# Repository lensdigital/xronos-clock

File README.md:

Xronos (from greek Χρόνος [kronos] which means Time) Clock is not your average Alarm clock.  
It’s open source, hackable and customizable device.  
It has a stylish look, hand made, and it Talks! 
Heck it will even tell you temperature inside your room or from a remote sensor!
Xronos has internal backup battery that will allow it to keep time if you forgot to plug in … if it’s just for an hour or … for a year or two!  
All settings are saved to flash memory (EEPROM), so you don’t have to worry about power loss. All your alarm settings and preference will be there when power comes back on!
Since all audio files are kept on SD card inside, you can even change alarm tones, or replace voice prompts with your own
Xronos has 3 cool looking durable arcade buttons that give you simple access to all of it’s features.

Note: Please do not use V2 for Xronos 2 Clock anymore. V2 Firmware is no longer maintained, but V3 will work with Xronos 2 Clock as well as with upcoming Xronos 3 clocks.

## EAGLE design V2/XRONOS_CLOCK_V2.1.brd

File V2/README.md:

V2 is No longer supported or updated.  Please use V3 firmware as it has backwards compability to Xronos 2 clocks.

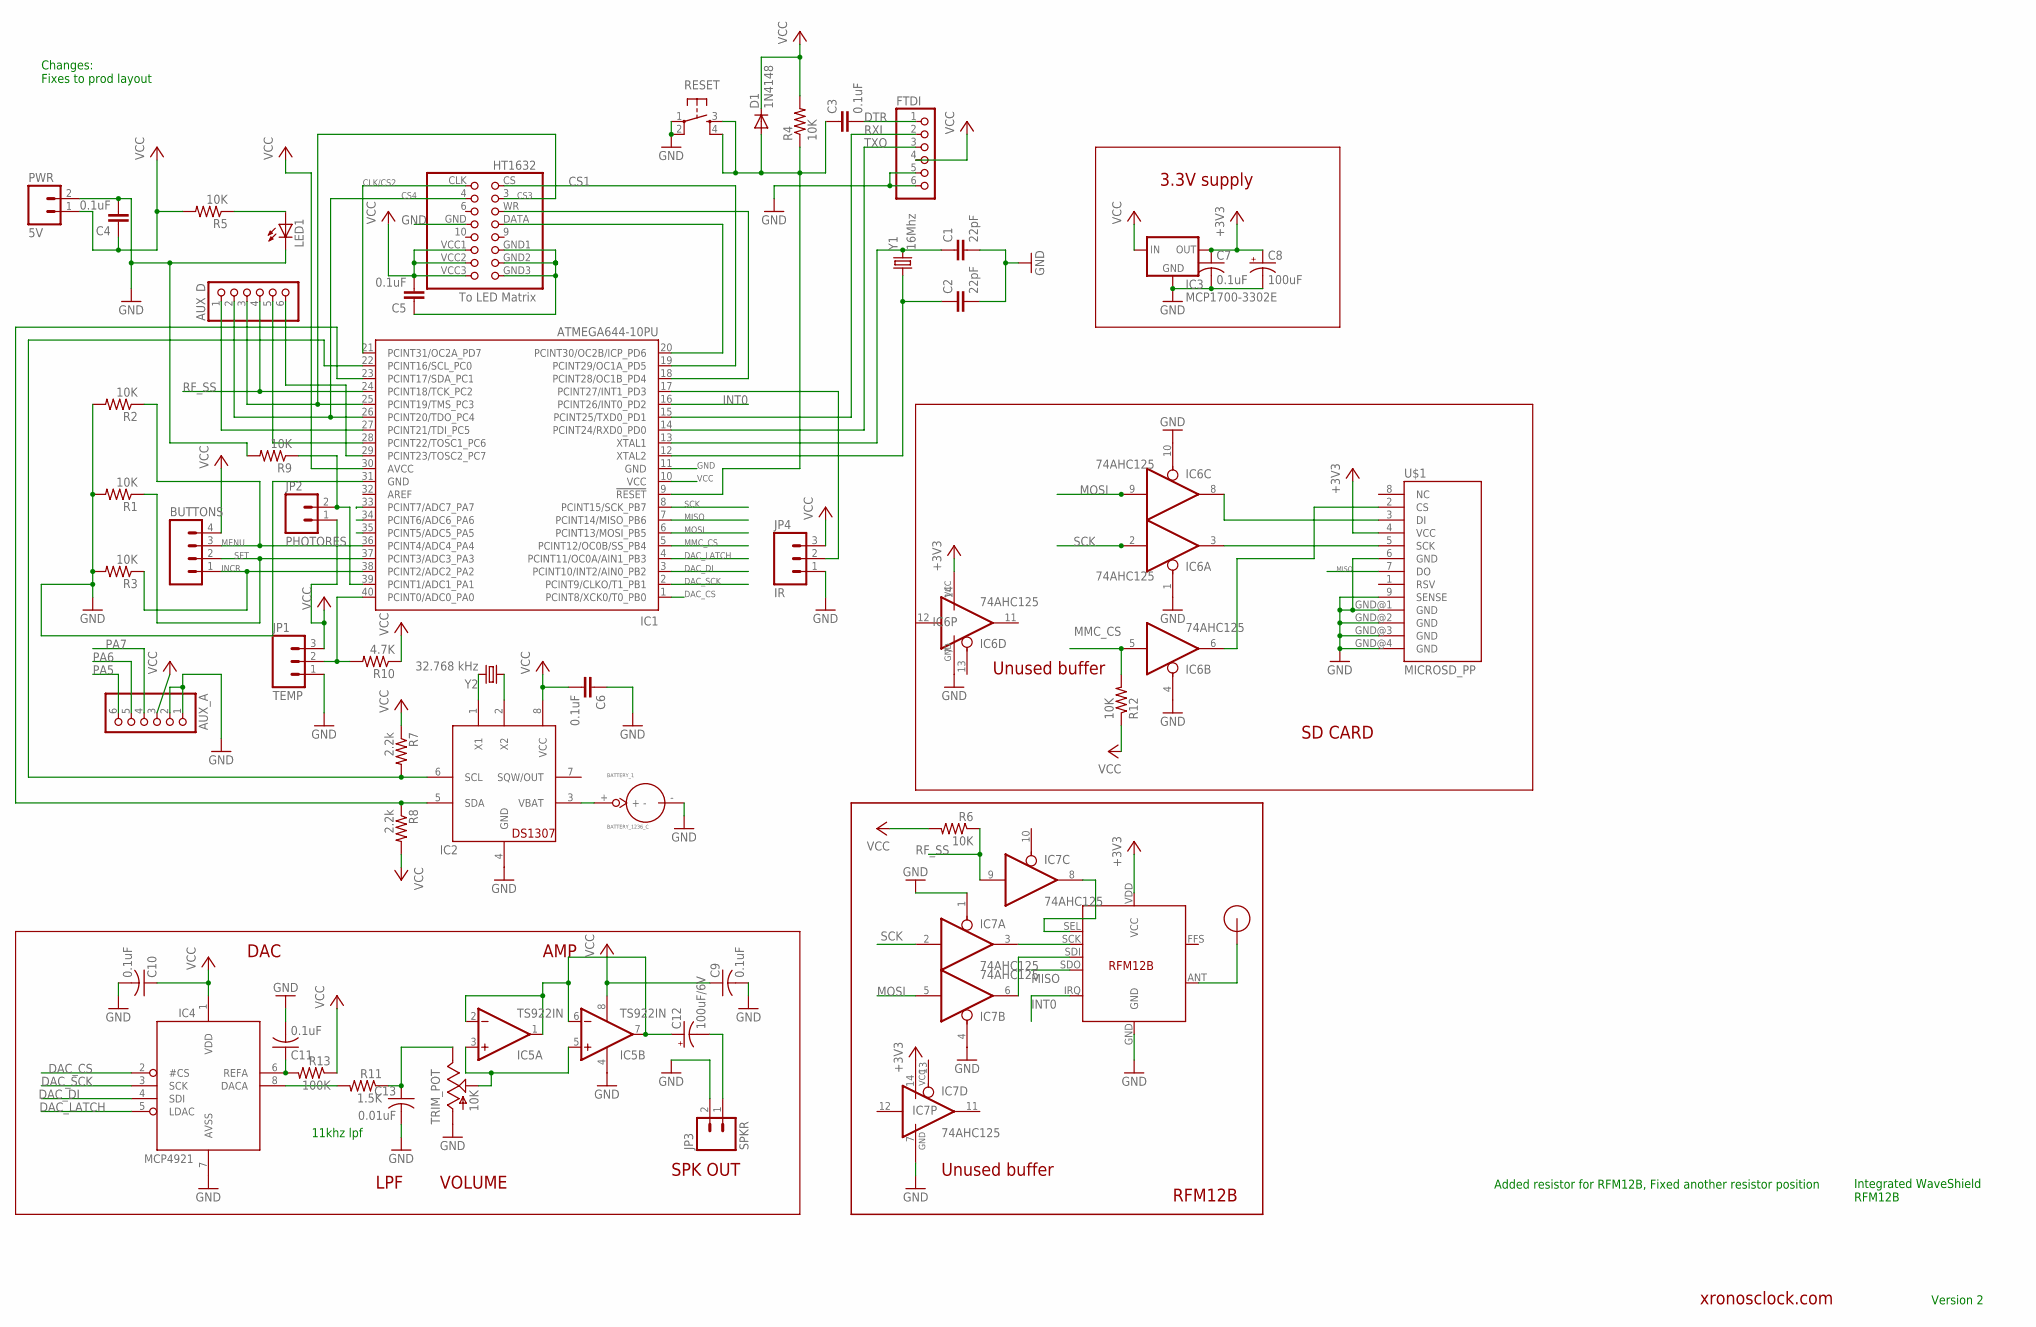
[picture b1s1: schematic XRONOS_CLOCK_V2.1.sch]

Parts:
AUX_A: PINHD-1X6; 1X06
AUX_D: PINHD-1X6; 1X06
BATTERY_1: BATTERY_1236_C
BUTTONS: M04POLAR; MOLEX-1X4
C1, C2: 22pF; C025-024X044
C3, C4, C5, C6: 0.1uF; C025-024X044
C7, C9, C10, C11: 0.1uF; C025-025X050
C8: 100uF; E2,5-5
C12: 100uF/6V; E2,5-5
C13: 0.01uF; C025-025X050
D1: 1N4148; DO35-7
FTDI: PINHD-1X6; 1X06
HT1632: To LED Matrix; IDC2X08
IC1: ATMEGA644-10PU; DIL40
IC2: DS1307; DIL08
IC3: MCP1700-3302E; TO92
IC4: MCP4921; DIL08
IC5: TS922IN; DIL08
IC6: 74AHC125; DIL14-LARDO
IC7: 74AHC125; DIL14
JP1: TEMP; MOLEX-1X3
JP2: PHOTORES; MOLEX-1X2
JP3: SPKR; MOLEX-1X2
JP4: IR; MOLEX-1X3_LOCK
LED1: LED-3MM-NO_SILK; LED3MM-NS
PWR: 5V; MOLEX-1X2
R1, R2, R3, R4, R5, R9: 10K; AXIAL-0.3EZ
R6, R12: 10K; AXIAL-0.3
R7, R8: 2.2k; AXIAL-0.3EZ
R10: 4.7K; AXIAL-0.3EZ
R11: 1.5K; AXIAL-0.3
R13: 100K; AXIAL-0.3
RESET: TAC_SWITCHPTH; TACTILE-PTH
TRIM_POT: 10K; B25P
U$1: MICROSD_PP
U$2: RFM12B
U$3: RFM12B_ANTENNA; RFM12B-ANTENNA
Y1: 16Mhz; HC49US
Y2: 32.768 kHz; TC26HEZ

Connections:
+3V3: C7.1, C8.+, IC3.3 (OUT), IC6.14 (VCC), IC7.14 (VCC), U$1.4 (VCC), U$2.VDD (VCC)
ADJ: IC1.40 (PCINT0/ADC0_PA0), JP1.2, R10.P$2 (2)
CLK/CS2: HT1632.CLK (2), IC1.21 (PCINT31/OC2A_PD7)
CS1: HT1632.CS (1), IC1.19 (PCINT29/OC1A_PD5)
CS3: AUX_D.3, HT1632.3, IC1.25 (PCINT19/TMS_PC3)
CS4: AUX_D.2, HT1632.4, IC1.26 (PCINT20/TDO_PC4)
DAC_CS: IC1.1 (PCINT8/XCK0/T0_PB0), IC4.2 (#CS)
DAC_DI: IC1.3 (PCINT10/INT2/AIN0_PB2), IC4.4 (SDI)
DAC_LATCH: IC1.4 (PCINT11/OC0A/AIN1_PB3), IC4.5 (LDAC)
DAC_SCK: IC1.2 (PCINT9/CLKO/T1_PB1), IC4.3 (SCK)
DATA: HT1632.DATA (7), IC1.20 (PCINT30/OC2B/ICP_PD6)
DTR: C3.2, FTDI.1
GND: AUX_A.1, AUX_A.2, BATTERY_1.-, C1.2, C2.2, C4.2, C6.1, C7.2, C8.-, C9.2, C10.2, C11.2, C13.2, FTDI.5, FTDI.6, HT1632.GND (8), IC1.11 (GND), IC1.31 (GND), IC2.4 (GND), IC3.1 (GND), IC4.7 (AVSS), IC5.4 (V-), IC6.1 (OE), IC6.4 (OE), IC6.7 (GND), IC6.10 (OE), IC7.1 (OE), IC7.4 (OE), IC7.7 (GND), JP1.1, JP3.2, JP4.1, LED1.K (C), PWR.2, R1.P$2 (2), R2.P$2 (2), R3.P$2 (2), R9.P$2 (2), RESET.1, RESET.2, TRIM_POT.A, U$1.6 (GND), U$1.9 (SENSE), U$1.GND@1 (GND), U$1.GND@2 (GND), U$1.GND@3 (GND), U$1.GND@4 (GND), U$2.GND
INCR: BUTTONS.1, IC1.38 (PCINT2/ADC2_PA2), R3.P$1 (1)
INT0: IC1.16 (PCINT26/INT0_PD2), U$2.IRQ
MENU: BUTTONS.3, IC1.36 (PCINT4/ADC4_PA4), R2.P$1 (1)
MISO: IC1.7 (PCINT14/MISO_PB6), U$1.7 (DO), U$2.SDO
MMC_CS: IC1.5 (PCINT12/OC0B/SS_PB4), IC6.5 (I), R12.P$2 (2)
MOSI: IC1.6 (PCINT13/MOSI_PB5), IC6.9 (I), IC7.5 (I)
unnamed: U$2.ANT, U$3.P$1
unnamed: C5.1, HT1632.GND1 (11), HT1632.GND2 (13), HT1632.GND3 (15)
unnamed: IC2.2 (X2), Y2.1
unnamed: IC2.1 (X1), Y2.2
unnamed: C1.1, IC1.13 (XTAL1), Y1.2
unnamed: BATTERY_1.+, IC2.3 (VBAT)
unnamed: IC7.8 (O), U$2.SEL
unnamed: IC1.17 (PCINT27/INT1_PD3), JP4.2
unnamed: C2.1, IC1.12 (XTAL2), Y1.1
unnamed: AUX_D.1, IC1.27 (PCINT21/TDI_PC5)
unnamed: IC1.39 (PCINT1/ADC1_PA1), JP2.2, R9.P$1 (1)
unnamed: AUX_D.5, IC1.28 (PCINT22/TOSC1_PC6)
unnamed: AUX_D.6, IC1.29 (PCINT23/TOSC2_PC7)
unnamed: IC6.8 (O), U$1.3 (DI)
unnamed: LED1.A, R5.P$1 (1)
unnamed: IC6.3 (O), U$1.5 (SCK)
unnamed: IC6.6 (O), U$1.2 (CS)
unnamed: IC4.8 (DACA), R11.P$2 (2)
unnamed: C12.-, JP3.1
unnamed: C12.+, IC5.1 (OUT), IC5.2 (-IN), IC5.6 (-IN), IC5.7 (OUT)
unnamed: C11.1, IC4.6 (REFA), R13.P$2 (2)
unnamed: IC5.3 (+IN), IC5.5 (+IN), TRIM_POT.S
unnamed: C13.1, R11.P$1 (1), TRIM_POT.E
unnamed: IC7.6 (O), U$2.SDI
unnamed: IC7.3 (O), U$2.SCK
PA5: AUX_A.6, IC1.35 (PCINT5/ADC5_PA5)
PA6: AUX_A.5, IC1.34 (PCINT6/ADC6_PA6)
PA7: AUX_A.4, IC1.33 (PCINT7/ADC7_PA7)
RESET: C3.1, D1.A, IC1.9 (!RESET), R4.P$1 (1), RESET.3, RESET.4
RF_SS: AUX_D.4, IC1.24 (PCINT18/TCK_PC2), IC7.9 (I), R6.P$1 (1)
RXI: FTDI.2, IC1.15 (PCINT25/TXD0_PD1)
SCK: IC1.8 (PCINT15/SCK_PB7), IC6.2 (I), IC7.2 (I)
SCL: IC1.23 (PCINT17/SDA_PC1), IC2.5 (SDA), R8.P$1 (1)
SDA: IC1.22 (PCINT16/SCL_PC0), IC2.6 (SCL), R7.P$2 (2)
SET: BUTTONS.2, IC1.37 (PCINT3/ADC3_PA3), R1.P$1 (1)
TXO: FTDI.3, IC1.14 (PCINT24/RXD0_PD0)
VCC: AUX_A.3, BUTTONS.4, C4.1, C5.2, C6.2, C9.1, C10.1, D1.C, FTDI.4, HT1632.VCC1 (12), HT1632.VCC2 (14), HT1632.VCC3 (16), IC1.10 (VCC), IC1.30 (AVCC), IC2.8 (VCC), IC3.2 (IN), IC4.1 (VDD), IC5.8 (V+), JP1.3, JP2.1, JP4.3, PWR.1, R4.P$2 (2), R5.P$2 (2), R6.P$2 (2), R7.P$1 (1), R8.P$2 (2), R10.P$1 (1), R12.P$1 (1), R13.P$1 (1)
WR: HT1632.WR (5), IC1.18 (PCINT28/OC1B_PD4)

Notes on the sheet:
Version 2
Changes: Fixes to prod layout
Integrated WaveShield RFM12B
11khz lpf
DAC
VOLUME
LPF
AMP
SPK OUT
SD CARD
3.3V supply
Unused buffer
RFM12B
xronosclock.com
Added resistor for RFM12B, Fixed another resistor position

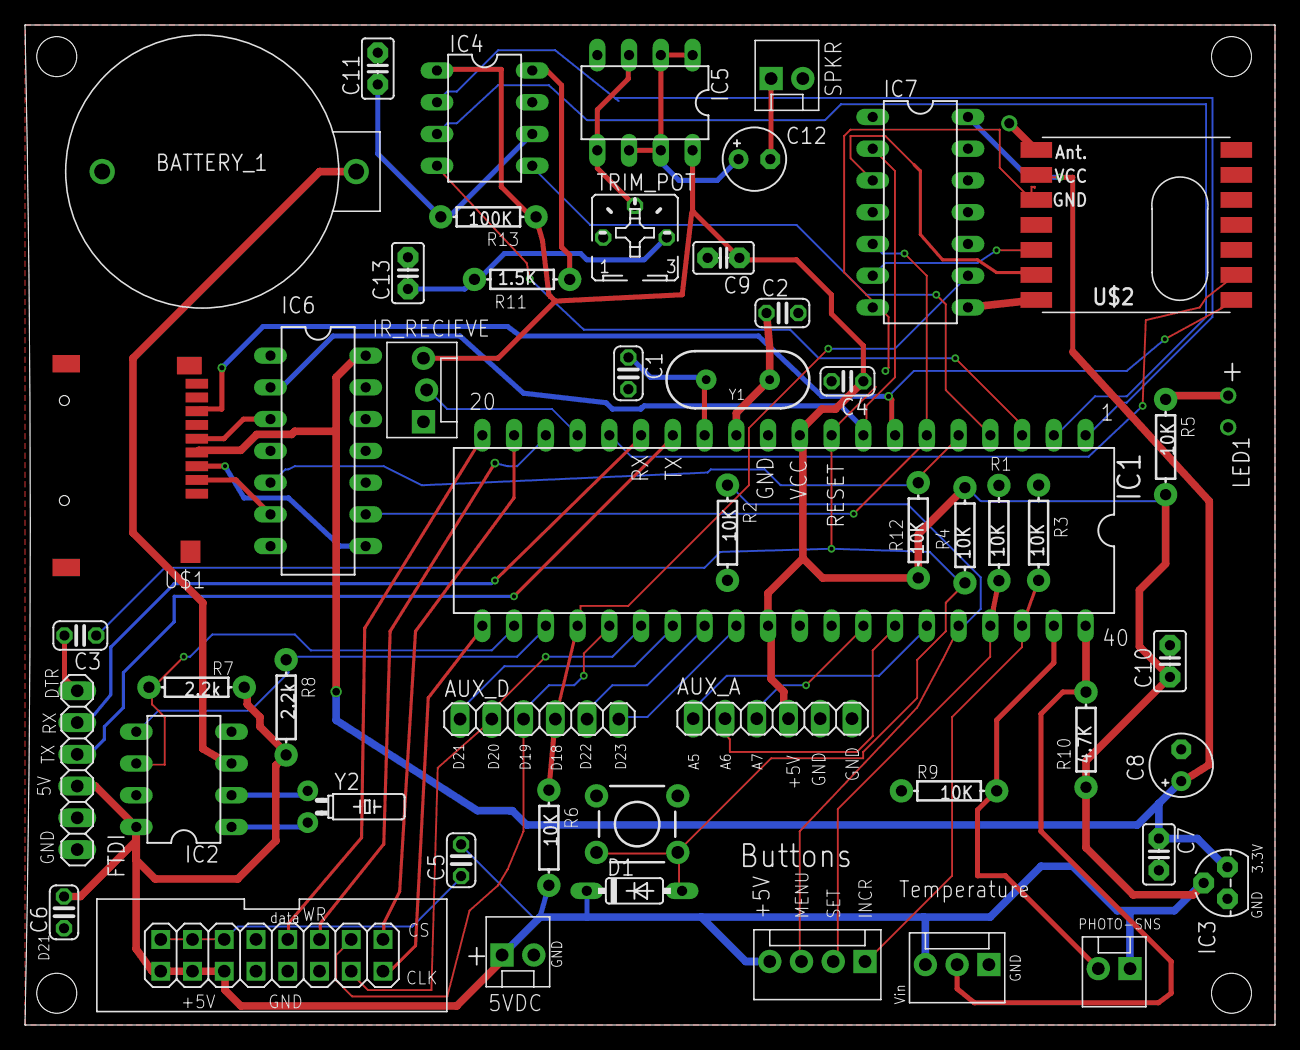
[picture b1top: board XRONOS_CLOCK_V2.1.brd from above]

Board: 2 copper layers, 100.0 x 80.0 mm, 53 parts (0 on the bottom side), 57 nets.

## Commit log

2016-03-01 V2_16
2016-03-01 Uploaded design files
2016-03-01 Uploaded Firmware files
2016-08-08 First version
2016-08-08 Arduino Version Note
2016-08-08 Avrdude and Arduino version notice
2016-08-14 Added list of issues
2016-08-14 Fixes
    Fixed incorrect time display in 12hr mode.
2016-08-14 Time 12h fix
2016-08-18 Bugfix
    Fix bug with single digit humidity not showing correctly
2016-11-02 V3.03: Added UTC Timezone
2016-11-03 Bug fix
2016-11-03 Bug fixes
    Fix for RFM12b radio.
    Fix for EEPROM Reset menu item.
2016-11-03 RFM12b Fix
    Modified pin mappings for IRQ, etc.
2016-11-07 V3.05
    Fix Radio Stats display and RF indicator
    Fix QuickMenu Alarm announcement
2016-11-07 V3.05 Bug fixes
    V05: Fix Radio stats, fix QuickMenu (alarm not annoused)
2016-11-07 V3.06 (Radio Stats)
    Updated to show datestamp of last radio recieve if it's been too long
    since last transmission.
2016-11-07 Fix Github garbage
    Github for desktop completely messed up my code :(
2016-11-17 V 3.08
    Fixed ext. temperature display bug and few others.
    Replaced TH02 with SI7021 sensor (for Xronos 3 boards).
2016-11-17 Si7021 Sensor replaced TH02
2016-11-17 V3.08
2017-02-08 V8 bug fixes, new features
    Major rewrite of all message scrolling functions.
    Display for Radio status and sensor battery level.
    Attempt at fixing temperature bug
2017-02-09 V9: Fix temperature sensor
    Fix external (radio) sensor temperature not showing correctly.
2017-02-09 V9
    External Tempreature sensor fix
2017-02-19 V10
    Fix for temperature/humidity stats. Sender ID Check
2017-02-19 Updated to latest
2017-02-26 V.11
    User now has control over what to show on scrolling display. New menu
    option to show or not RF sensor stats.
2017-04-01 V 3.09
    - Possible Fix for incorrect temperature from external sensor.
    - Added V3 hex firmware version compatible with Xronos 2 Clock

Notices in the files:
parts and their libraries:
SparkFun-Electromechanical: Licensing: CC v3.0 Share-Alike You are welcome to use this library for commercial purposes.
